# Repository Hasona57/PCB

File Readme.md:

# PCB Projects

This repository contains custom PCB designs created using KiCad. It includes schematic files, PCB layouts,and manufacturing-ready files.

## How to Use

1. Open `.kicad_sch` and `.kicad_pcb` files in KiCad
2. Modify as needed
3. Export Gerber files
4. Send to a PCB manufacturer
5. Solder components and test the board

## PCB Preview

## License

This project is licensed under the MIT License.

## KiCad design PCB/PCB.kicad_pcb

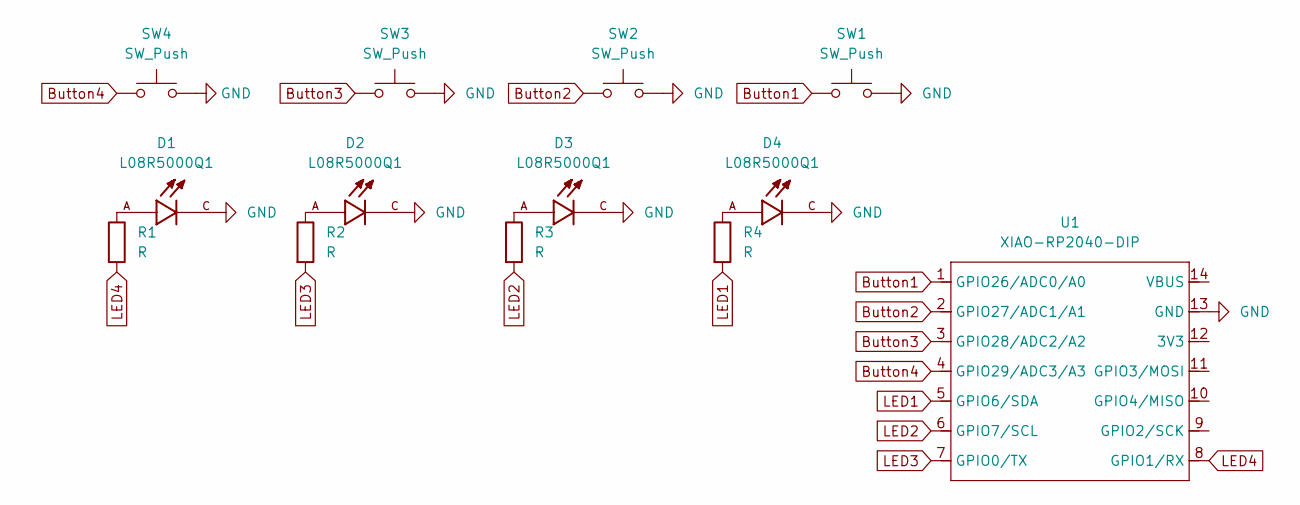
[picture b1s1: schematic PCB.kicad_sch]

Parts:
D1, D2, D3, D4: L08R5000Q1; LEDRD254W57D500H1070; PARTREV NA
R1, R2, R3, R4: R; R_Axial_DIN0204_L3.6mm_D1.6mm_P5.08mm_Horizontal
SW1, SW2, SW3, SW4: SW_Push; SW_Cherry_MX_1.00u_PCB
U1: XIAO-RP2040-DIP

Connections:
Button1: SW1.1, U1.1 (GPIO26/ADC0/A0)
Button2: SW2.1, U1.2 (GPIO27/ADC1/A1)
Button3: SW3.1, U1.3 (GPIO28/ADC2/A2)
Button4: SW4.1, U1.4 (GPIO29/ADC3/A3)
GND: D1.C, D2.C, D3.C, D4.C, SW1.2, SW2.2, SW3.2, SW4.2, U1.13 (GND)
LED1: R4.2, U1.5 (GPIO6/SDA)
LED2: R3.2, U1.6 (GPIO7/SCL)
LED3: R2.2, U1.7 (GPIO0/TX)
LED4: R1.2, U1.8 (GPIO1/RX)
unnamed: D1.A, R1.1
unnamed: D2.A, R2.1
unnamed: D3.A, R3.1
unnamed: D4.A, R4.1

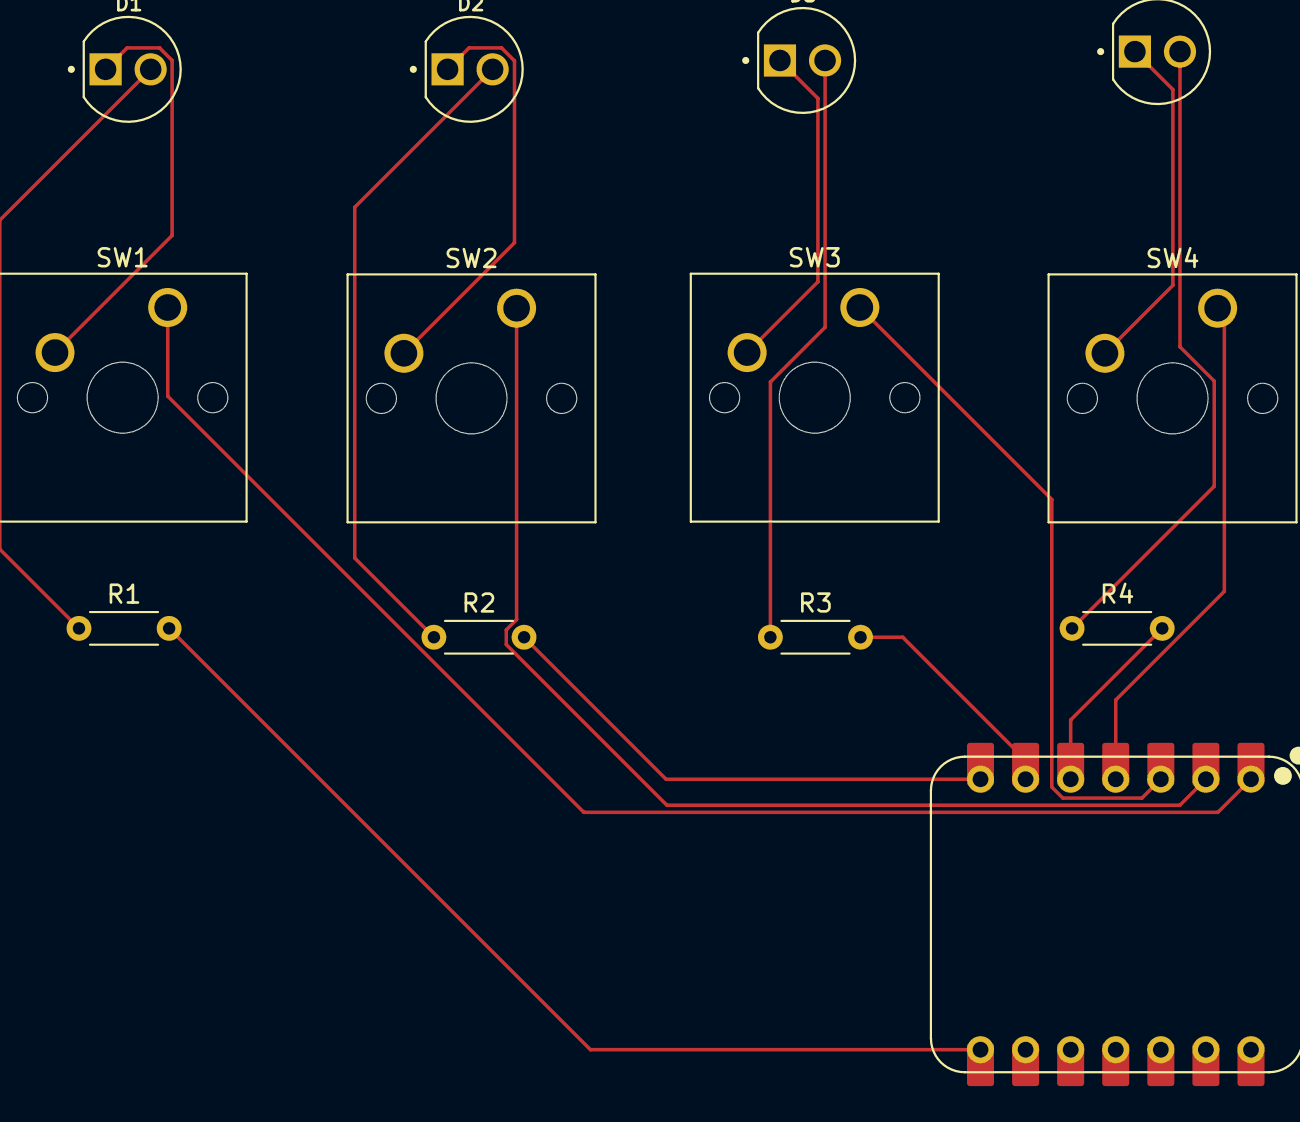
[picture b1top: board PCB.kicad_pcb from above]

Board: 2 copper layers, 13 parts (0 on the bottom side), 13 nets.

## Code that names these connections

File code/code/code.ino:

int BUT1 = 26;
int BUT2 = 27;
int BUT3 = 28;
int BUT4 = 29;

int LED1 = 6;
int LED2 = 7;
int LED3 = 0;
int LED4 = 1;

unsigned long t1 = 0;
unsigned long t2 = 0;
unsigned long t3 = 0;
bool h3 = false;

unsigned long t4 = 0;
int c4 = 0;

void setup() {
  pinMode(BUT1, INPUT_PULLUP);
  pinMode(BUT2, INPUT_PULLUP);
  pinMode(BUT3, INPUT_PULLUP);
  pinMode(BUT4, INPUT_PULLUP);

  pinMode(LED1, OUTPUT);
  pinMode(LED2, OUTPUT);
  pinMode(LED3, OUTPUT);
  pinMode(LED4, OUTPUT);
}

void loop() {
  unsigned long now = millis();

  if (digitalRead(BUT1) == LOW) {
    t1 = now;
    digitalWrite(LED1, HIGH);
  } else {
    digitalWrite(LED1, LOW);
  }

  if (digitalRead(BUT2) == LOW) {
    t2 = now;
  }

  if (t2 - t1 <= 2000 && t2 != 0 && t1 != 0) {
    digitalWrite(LED2, HIGH);
  } else {
    digitalWrite(LED2, LOW);
  }

  if (digitalRead(BUT3) == LOW) {
    if (!h3) {
      t3 = now;
      h3 = true;
    } else if (now - t3 >= 800) {
      digitalWrite(LED3, HIGH);
    }
  } else {
    h3 = false;
    digitalWrite(LED3, LOW);
  }

  if (digitalRead(BUT4) == LOW) {
    if (now - t4 < 400) {
      c4++;
    } else {
      c4 = 1;
    }
    t4 = now;
    delay(200);
  }

  if (c4 == 2) {
    digitalWrite(LED4, HIGH);
    c4 = 0;
  } else {
    digitalWrite(LED4, LOW);
  }
}

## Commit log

2025-07-29 Rename Screenshot from 2025-07-29 05-48-24.png to front.png
2025-07-29 Rename Screenshot from 2025-07-29 05-48-46.png to Back.png
2025-07-29 Rename Screenshot from 2025-07-29 05-49-02.png to PCB.png
2025-07-29 gerbers
2025-07-29 code
